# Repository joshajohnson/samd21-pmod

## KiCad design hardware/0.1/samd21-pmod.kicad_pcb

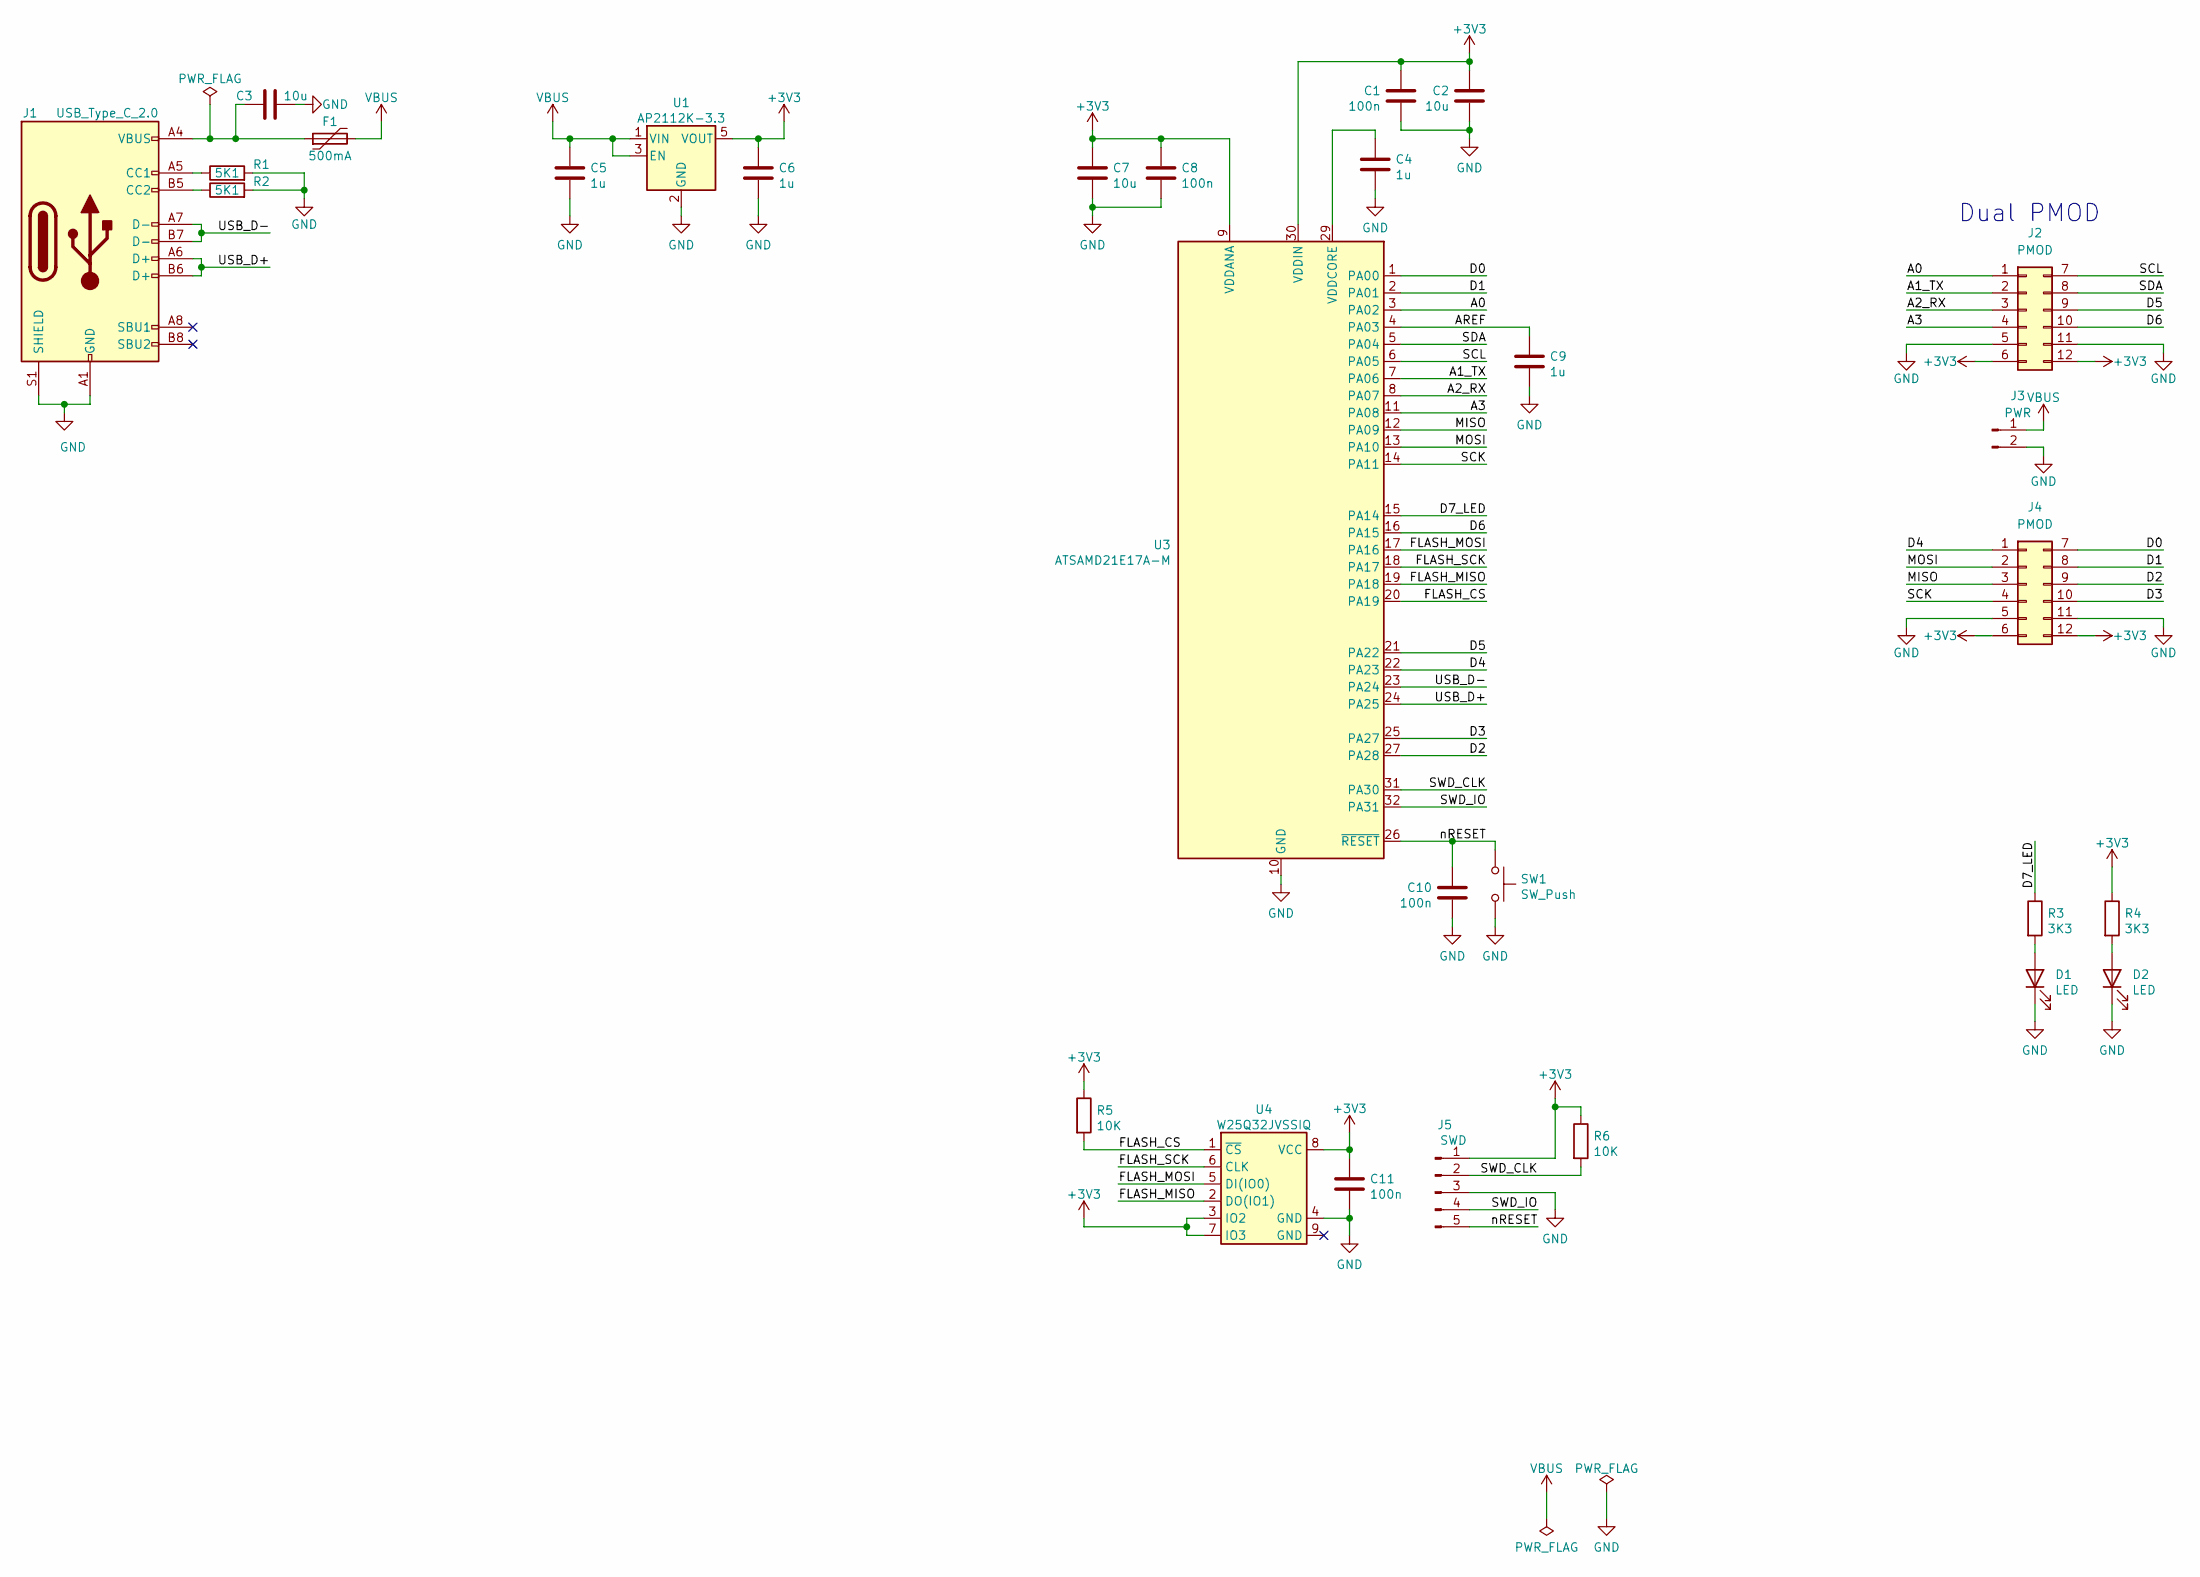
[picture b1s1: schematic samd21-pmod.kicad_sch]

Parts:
C1, C8, C10, C11: 100n; C_0603_1608Metric
C2, C3, C7: 10u; C_0603_1608Metric
C4, C5, C6, C9: 1u; C_0603_1608Metric
D1, D2: LED; LED_0603_1608Metric
F1: 500mA; Fuse_0603_1608Metric
J1: USB_Type_C_2.0; USB_C_Receptacle_HRO_TYPE-C-31-M-12
J2, J4: PMOD; PMOD_HOST
J3: PWR; PinSocket_1x02_P2.54mm_Vertical
J5: SWD; 5_PIN_THT_Staggered
R1, R2: 5K1; R_0603_1608Metric
R3, R4: 3K3; R_0603_1608Metric
R5, R6: 10K; R_0603_1608Metric
SW1: SW_Push; SW_Push_KMR2
U1: AP2112K-3.3; SOT-23-5
U3: ATSAMD21E17A-M; QFN-32-1EP_5x5mm_P0.5mm_EP3.6x3.6mm
U4: W25Q32JVSSIQ; SOP-8_5.28x5.23mm_P1.27mm

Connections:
+3V3: C1.1, C2.1, C6.1, C7.1, C8.1, C11.1, J2.6, J2.12, J4.6, J4.12, J5.1, R4.1, R5.1, R6.1, U1.5 (VOUT), U3.9 (VDDANA), U3.30 (VDDIN), U4.3 (IO2), U4.7 (IO3), U4.8 (VCC)
/A0: J2.1, U3.3 (PA02)
/A1_TX: J2.2, U3.7 (PA06)
/A2_RX: J2.3, U3.8 (PA07)
/A3: J2.4, U3.11 (PA08)
/AREF: C9.1, U3.4 (PA03)
/D0: J4.7, U3.1 (PA00)
/D1: J4.8, U3.2 (PA01)
/D2: J4.9, U3.27 (PA28)
/D3: J4.10, U3.25 (PA27)
/D4: J4.1, U3.22 (PA23)
/D5: J2.9, U3.21 (PA22)
/D6: J2.10, U3.16 (PA15)
/D7_LED: R3.1, U3.15 (PA14)
/FLASH_CS: R5.2, U3.20 (PA19), U4.1 (~CS)
/FLASH_MISO: U3.19 (PA18), U4.2 (DO(IO1))
/FLASH_MOSI: U3.17 (PA16), U4.5 (DI(IO0))
/FLASH_SCK: U3.18 (PA17), U4.6 (CLK)
/MISO: J4.3, U3.12 (PA09)
/MOSI: J4.2, U3.13 (PA10)
/SCK: J4.4, U3.14 (PA11)
/SCL: J2.7, U3.6 (PA05)
/SDA: J2.8, U3.5 (PA04)
/SWD_CLK: J5.2, R6.2, U3.31 (PA30)
/SWD_IO: J5.4, U3.32 (PA31)
/USB_D+: J1.A6 (D+), J1.B6 (D+), U3.24 (PA25)
/USB_D-: J1.A7 (D-), J1.B7 (D-), U3.23 (PA24)
/nRESET: C10.1, J5.5, SW1.1, U3.26 (~RESET)
GND: C1.2, C2.2, C3.2, C4.2, C5.2, C6.2, C7.2, C8.2, C9.2, C10.2, C11.2, D1.1 (K), D2.1 (K), J1.A1 (GND), J1.A12 (GND), J1.B1 (GND), J1.B12 (GND), J1.S1 (SHIELD), J2.5, J2.11, J3.2, J4.5, J4.11, J5.3, R1.2, R2.2, SW1.2, U1.2 (GND), U3.10 (GND), U3.28 (GND), U3.33 (EP), U4.4 (GND)
unnamed: C4.1, U3.29 (VDDCORE)
unnamed: D1.2 (A), R3.2
unnamed: D2.2 (A), R4.2
unnamed: C3.1, F1.1, J1.A4 (VBUS), J1.A9 (VBUS), J1.B4 (VBUS), J1.B9 (VBUS)
unnamed: J1.A5 (CC1), R1.1
unnamed: J1.B5 (CC2), R2.1
VBUS: C5.1, F1.2, J3.1, U1.1 (VIN), U1.3 (EN)

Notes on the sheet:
Dual PMOD

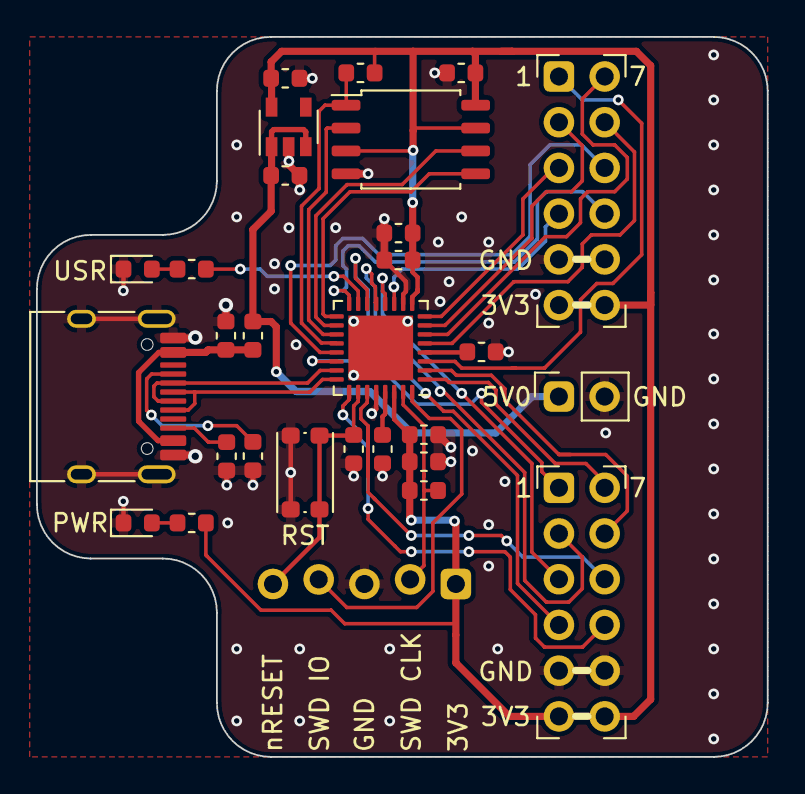
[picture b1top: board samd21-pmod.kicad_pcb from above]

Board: 2 copper layers, 40.6 x 40.0 mm, 29 parts (0 on the bottom side), 36 nets.

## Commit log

2021-06-01 add gitignore
2021-06-01 initial layout complete
2021-06-03 tidy up routing
